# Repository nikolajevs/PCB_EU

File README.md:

# PCB_EU — контроллер гроубокса

Самостоятельный проект платы EU-0.1 и прошивки для ESP32-WROOM-32E-N4 (4 МБ flash, без PSRAM).

- [Аппаратная часть](hardware/PCB_EU/README.md): схема, плата, BOM, библиотеки, 3D-модели и результаты проверок.
- [Решения и ограничения](hardware/PCB_EU/DESIGN.md): питание, GPIO, механика и оставшиеся испытания.
- [Прошивка и инструкции сборки](softwareEU/README.md): климат, свет, вентиляторы, полив, RTC MCP7940N, INA226 и веб-интерфейс.
- [Трафареты для паяльной пасты](hardware/stencil/README.md): два печатных трафарета (верх и низ) под сопло 0,2 мм; не печатались.
- [Проект KiCad](hardware/PCB_EU/PCB_EU.kicad_pro): открывать в KiCad **10.0.7**.
- [EU-LITE](hardware/PCB_EU_LITE/README.md): удешёвленный аналог EU-0.1 из деталей со склада (один LED-канал, без тахометров), RGB-светодиод статуса, схема и BOM без PCB; закупка 34,68 € по каталогу от 23.10.2026 (RGB-светодиода в каталоге нет, оценка до 0,50 €).

## Состояние

Исходники перенесены 23.10.2026 из [nikolajevs/ai, коммит 390374e](https://github.com/nikolajevs/ai/tree/390374ec6d7405bd25f6ed4380bc14fe30cf3cde), включая исправления документации из [PR #93](https://github.com/nikolajevs/ai/pull/93). Затем 24.10.2026 перенесён [PR #94](https://github.com/nikolajevs/ai/pull/94) того же репозитория ([коммит 7fa9410](https://github.com/nikolajevs/ai/tree/7fa9410ddb7977c46e313506acb037693ad571e1)): D501/D601 — SS8PH10-M3/86A, J201 — ZL201-10G, клеммы DG306/DG301R без запаса; оценка закупки 84,67 € → 81,25 €. История предыдущей разработки остаётся в исходном репозитории; номера прежних PR в документации относятся к нему. PCB_V1, её прошивка и инфраструктура VPS в этот репозиторий не входят.

Сохранённые аппаратные отчёты относятся к полному прогону KiCad 10.0.7 от 23.10.2026, выполненному в исходном репозитории (PR #94): ERC и DRC без ошибок, плата полностью разведена. Повторный прогон в этом репозитории 24.10.2026 дал тот же результат, но не сохранялся. 24.10.2026 подготовлены Gerber и сверловка для платы из коммита `b3f286d`; Игорь подтвердил размещение заказа. [Заказанный архив и отчёт проверок](hardware/PCB_EU/README.md#заказ-платы-24102026) сохранены в репозитории. Испытания на реальной плате ещё предстоят.

**EU-LITE** (24.10.2026) — отдельный проект в `hardware/PCB_EU_LITE/`; EU-0.1 и заказанная плата не затронуты. Схема и BOM EU-LITE проверены только скриптами без KiCad; ERC, PCB и прошивка для неё ещё не выполнялись.

Радиатор Q501 крепится на двух запаянных ножках и винте М3 с изолирующей прокладкой и втулкой. Физическая примерка и проверка изоляции выполняются на прототипе.

## Проверки и сборка

Команды выполняются из корня репозитория. Для базовых проверок нужны Python 3 и Node.js:

```sh
python hardware/PCB_EU/tools/generate.py
python hardware/PCB_EU/tools/verify.py hardware/PCB_EU/review/netlist.xml
node --test tests/settings.test.cjs
```

Полная аппаратная проверка требует KiCad 10.0.7, Python с `pcbnew` той же версии и Shapely 2:

```sh
python hardware/PCB_EU/tools/run_checks.py --kicad-cli /path/to/kicad-cli --kicad-python /path/to/python-with-pcbnew
```

Общий скрипт `hardware/check_fab.py` включён в репозиторий: его вызывает `run_checks.py`. Исторические упоминания PCB_V1 в комментариях описывают происхождение кода, внешняя копия PCB_V1 для запуска не нужна. Все библиотеки и 3D-модели проекта находятся внутри `hardware/PCB_EU/libraries/`.

Сборка прошивки после установки зависимостей из [softwareEU/README.md](softwareEU/README.md#сборка-и-проверки):

```sh
arduino-cli compile --fqbn esp32:esp32:esp32 softwareEU
```

Файлы `softwareEU/data/` загружаются в SPIFFS отдельно. Список стендовых испытаний приведён в инструкции прошивки.

Проверки при переносе: 23.10.2026 — генерация без содержательных изменений, 56 проверок соединений и закупки, 10 тестов веб-интерфейса, проверка локальных ссылок и синтаксиса Python; полный аппаратный прогон тогда не повторялся. 24.10.2026 (PR #94) — то же и полный `run_checks.py` на KiCad 10.0.7; сохранённые отчёты `review/` отличаются от нового прогона только датами и путём в `netlist.xml`, поэтому не перезаписывались. На момент прогона контрольные суммы всех 123 исходников из `review/validation.json` совпадали с файлами. После уточнения BOM 24.10.2026 (домашние хидеры, поштучная продажа INA226, актуальные примечания) BOM и скрипты изменены; сохранённые контрольные суммы и сводка закупки относятся к предыдущему состоянию. Подробности — в README аппаратной части; схема и PCB не менялись. Сборка прошивки не выполнялась. Окончания строк текста закреплены в `.gitattributes`, исходные байты моделей STEP/STP сохраняются.

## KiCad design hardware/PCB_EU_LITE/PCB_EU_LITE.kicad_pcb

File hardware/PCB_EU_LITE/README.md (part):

# EU-LITE — дешёвый аналог EU-0.1 из деталей со склада

**Состояние на 26.10.2026: документация согласована с текущими исходниками; стендовые испытания не выполнены.** Плата 100×100 мм, четыре слоя, 163 посадки. Исправлены силовая медь входа и LED-каскада, переходные в пасте и локальная земля ESP32. Подключение Q102/Q701/Q702/Q703, ST1S14 и ST1S10 сохранено: замечание о перепутанных выводах снято.

**Выпуск изготовления пока не закрыт.** Последний полный прогон KiCad 10.0.7 сохранён в [review/power-copper-2026-10-26/](review/power-copper-2026-10-26/), но предшествует исправлению подписи F103. Сейчас схема содержит `6.3 A fast`, плата — старое поле `6.3 A slow`: электрические соединения совпадают, строгий паритет и `fabricate.py` не проходят из-за этого поля. Gerber r1/r2 устарели относительно текущей меди. Перед изготовлением нужно согласовать поле F103, повторить полный профиль и выпустить новый комплект Gerber/Excellon. Эта редакция документации схему, плату, BOM и отчёты проверок не изменяет.

Проект по образцу [cheap-version](https://github.com/nikolajevs/ai/tree/7fa9410ddb7977c46e313506acb037693ad571e1/hardware/cheap-version) (дешёвая PCB_V1 из того же склада): всё, что есть на складе владельца ([stock/sklad-2026-10-24.csv](stock/sklad-2026-10-24.csv)), берётся оттуда; недостающее — из [снимка каталога цен Salvats / Electrobase от 23.10.2026](procurement_lite.json). Отличия от EU-0.1, расчёты и открытые вопросы — в [DESIGN.md](DESIGN.md).

**F103:** `3413.0224.11` — SCHURTER **USI 1206, 6,3 А, Quick-Acting F (fast)** ([даташит](https://us.schurter.com/pdf/english/typ_usi_1206.pdf)). MPN и BOM сохранены; пуск LED и согласование I²t требуют измерения. F101 `3413.0330.11` и F102 `3413.0327.11` — UST 1206 time-lag; название карточки магазина не заменяет характеристику изготовителя.

## Что сохранено и что убрано

Сохранено: вход 24 В с защитой от переполюсовки и предохранителями, ESP32-WROOM-32E-N4 (те же GPIO), 12 В и 3,3 В, **один** LED-канал LM3429 (около 75 Вт / 1,55 А при 48 В суммарно на J501/J502/J503), **RGB-светодиод статуса** (GPIO4/16/17), PTC 100 Вт, помпа 24 В, два вентилятора 12 В с PWM, измерение мощности (INA238 вместо INA226), RTC MCP7940N с CR2032, microSD, SHT4x и поплавок.

Добавлено по просьбе владельца 24.10.2026: RGB-светодиод для индикации статуса и процессов (лист «Status»).

Убрано по решению владельца 24.10.2026: второй LED-канал (линейки) и тахометры вентиляторов. Дополнительно, для цены: аппаратная блокировка LED по UVLO/PGOOD (LM2903 + BAT54), USBLC6 на входе поплавка, ESD-диоды вентиляторов и радиатор с изоляцией. Последствия — в [DESIGN.md](DESIGN.md#отличия-от-eu-01) и [DESIGN.md, «Открытые вопросы»](DESIGN.md#открытые-вопросы).

## Файлы

| Файл | Назначение |
|---|---|
| [DESIGN.md](DESIGN.md) | Решения, отличия от EU-0.1, расчёты, склад без запаса, открытые вопросы |
| [PCB_EU_LITE.kicad_pro](PCB_EU_LITE.kicad_pro), [PCB_EU_LITE.kicad_sch](PCB_EU_LITE.kicad_sch) и 8 листов | Схема (KiCad 10, генерируется `tools/generate.py`) |
| [PCB_EU_LITE.kicad_pcb](PCB_EU_LITE.kicad_pcb), [placement.json](placement.json) | 163 посадки, четырёхслойная плата; статус паритета и изготовления — в разделе «Проверки» |
| [BOM_allocated.csv](BOM_allocated.csv), [BOM_allocated.json](BOM_allocated.json) | Склад (`stock`, с остатком после сборки) и докупка (`buy`, с URL и датой цены) |
| [procurement_lite.json](procurement_lite.json) | Снимок каталога с резисторами уставки LED 4,7 кОм/620 Ом и карточкой OSTAPA57E2A владельца |
| [stock/sklad-2026-10-24.csv](stock/sklad-2026-10-24.csv) | Склад владельца (копия присланной выгрузки) |
| [design.json](design.json) | Полная спецификация выводов, цепей и компонентов |
| [review/connectivity.txt](review/connectivity.txt) | Сохранённый предыдущий полный прогон; актуальные 58 проверок для 75 Вт описаны в разделе «Проверки» |
| [review/Bench_checklist.md](review/Bench_checklist.md) | Что измерить при первом включении |
| [review/silkscreen.json](review/silkscreen.json) | Аудит воспроизводимой сборочной шелкографии: размещённые, нативные и намеренно пропущенные метки |
| [libraries/](libraries) | Символы проекта; собственные посадки PowerDI5, DTMSS-27, VSSOP-10 и SOIC-8; локальная копия BC-2001 с узким коридором GND только для EU-LITE и локальные копии складских посадок; стандартные 3D-модели используют установленную библиотеку KiCad |
| [tools/route_power.py](tools/route_power.py), [tools/route_complete.py](tools/route_complete.py), [tools/route_progress.py](tools/route_progress.py), [tools/route_bt_ground.py](tools/route_bt_ground.py), [tools/route_rtc.py](tools/route_rtc.py), [tools/route_switch_stage.py](tools/route_switch_stage.py), [tools/route_ground_stitch.py](tools/route_ground_stitch.py), [tools/route_prune_stubs.py](tools/route_prune_stubs.py), [tools/route_led_source.py](tools/route_led_source.py), [tools/route_led_terminals.py](tools/route_led_terminals.py), [tools/silkscreen.py](tools/silkscreen.py) | Полигонная медь, воспроизводимые шаги частичной разводки и финальная сборочная шелкография |

`EU_Mechanical` и `EU_Parts` по-прежнему общие с EU-0.1 (`../PCB_EU/libraries`, см. `fp-lib-table`); исключение — `LITE_Mechanical:Battery_COMF_BC-2001`, локальная копия с коридором GND для батарейного контакта. Исходные библиотеки EU-0.1 не менялись.

## Закупка

**Electrobase** — 20,06 € с НДС (0,85 € — цена из карточки, присланной владельцем 25.10.2026)

| Деталь (артикул) | Шт. к покупке | Цена, € | Сумма, € | Позиции на плате |
|---|---:|---:|---:|---|
| [ABS07-32.768KHZ-7-T](https://electrobase.lv/katalogs/kvarca-generatori-tht/resonator-ceramic-32768khz-20ppm-7pf-smd-32x15x09mm) | 1 | 0.79 | 0.79 | Y301 |
| [AO3422](https://electrobase.lv/katalogs/tranzistori-ar-n-veida-kanalu-smd/transistor-n-mosfet-unipolar-55v-17a-800mw-sot23) | 5 (пачка по 5, нужно 3) | 0.26 | 1.30 | Q411 Q421 Q704 |
| [C1206C100J5GACTU](https://electrobase.lv/katalogs/kondensatori-mlcc-smd-0201/capacitor-ceramic-mlcc-10pf-50vdc-c0g-5-smd-1206) | 2 | 0.25 | 0.50 | C301 C302 |
| [ESP32-WROOM-32E-N4](https://electrobase.lv/katalogs/moduli-iot-wifi-bluetooth-lora/module-iot-bluetooth-low-energywifi-smd-0) | 1 | 7.48 | 7.48 | U202 |
| [JNRH1207-220M-A](https://electrobase.lv/katalogs/induktori-tht/inductor-wire-smd-22uh-ioper-54a-r-525o-30-isat-56a) | 1 | 0.54 | 0.54 | L101 |
| [OSTAPA57E2A](https://electrobase.lv/katalogs/diodes-led-tht-18mm/led-rgb-5mm-140deg-front-convex-231vdc-noof-term-4-round) | 1 | 0.85 | 0.85 | D901 |
| [LM3429MH/NOPB](https://electrobase.lv/katalogs/led-draiveri/ic-driver-boostbuck-boost-led-driver-htssop14-5a-372v-ch-1) | 1 | 4.86 | 4.86 | U501 |
| [MCP7940N-I/SN](https://electrobase.lv/katalogs/rtc-shemas/ic-rtc-circuit-i2c-sram-64bsram-1855vdc-so8-4085degc-tube-0) | 1 | 1.50 | 1.50 | U301 |
| [MEM2061-01-188-00-A](https://electrobase.lv/katalogs/savienojumi-kartem/connector-cards-microsd-push-push-smt-gold-flash-pin-8-0) | 1 | 1.74 | 1.74 | J301 |
| [SMBJ26A-E3/52](https://electrobase.lv/katalogs/diodes-transil-smd-vienvirziena/diode-tvs-600w-289319v-143a-unidirectional-5-smbj) | 1 | 0.50 | 0.50 | D101 |

**Salvats** — 12,56 € с НДС

| Деталь (артикул) | Шт. к покупке | Цена, € | Сумма, € | Позиции на плате |
|---|---:|---:|---:|---|
| [3403.0166.11](https://www.salvats.lv/lv/drosinataji-smd-10x3x3mm-umt-leni/1a-umt-drosinataji-leni-250vac125vdc-101x3x3mm-smd) | 1 | 0.75 | 0.75 | F105 |
| [3403.0169.11](https://www.salvats.lv/lv/drosinataji-smd-10x3x3mm-umt-leni/2a-umt-drosinataji-leni-250vac125vdc-101x3x3mm-smd) | 2 | 0.78 | 1.56 | F104 F401 |
| [3413.0224.11](https://www.salvats.lv/lv/drosinataji-smd-1206-32x16x06mm/drosinatajs-smd-1206-63a-63v-fast) | 1 | 0.86 | 0.86 | F103 |
| [3413.0327.11](https://www.salvats.lv/lv/drosinataji-smd-1206-32x16x06mm/drosinatajs-smd-1206-8a-63v-fast) | 1 | 0.80 | 0.80 | F102 |
| [3413.0330.11](https://www.salvats.lv/lv/drosinataji-smd-1206-32x16x06mm/drosinatajs-smd-1206-15a-63v-fast) | 1 | 0.75 | 0.75 | F101 |
| [BAT-CR2032/P](https://www.salvats.lv/lv/litija-baterijas/cr2032-litija-baterija-30v-o20x32mm-panasonic-442g) | 1 | 0.75 | 0.75 | комплектующее (CR2032 для BT301) |
| [BC-2001](https://www.salvats.lv/lv/baterijas-turetaji-1/bateriju-turetajs-metaliska-cemme-cr2032-1-baterija) | 1 | 0.33 | 0.33 | BT301 |
| [BC847B-DIO](https://www.salvats.lv/lv/npn-tranzistori-smd/bc847b1f-smd-tranzistors-npn-50v-01a-300mhz-sot23) | 4 | 0.06 | 0.24 | Q701 Q901 Q902 Q903 |
| [BC857B](https://www.salvats.lv/lv/pnp-tranzistori-smd/bc857b3f-smd-tranzistors-pnp-50v-01a-hfe220475-035w-200mhz-sot23) | 1 | 0.08 | 0.08 | Q702 |
| [BZV55C12](https://www.salvats.lv/lv/stabilitroni-smd-bzv55/12v-stabilitrons-smd-bzv55-5-05w-minimelf) | 1 | 0.13 | 0.13 | D103 |
| [C1206C102JCGACTU](https://www.salvats.lv/lv/kondensatori-keramiskie-smd-1206-1/1nf-1206-c0g-500v-5-smd-kondensators-1206) | 1 | 0.25 | 0.25 | C506 |
| [CL31C101JBCNNNC](https://www.salvats.lv/lv/kondensatori-keramiskie-smd-1206-1/100pf-1206-npo-50j-smd-kondensators-1206) | 1 | 0.07 | 0.07 | C507 |
| [CRCW1206620RFKTABC](https://www.salvats.lv/lv/rezistori-smd-1206-025w/620r-1206-1-smd-rezistors-1206) | 1 | 0.03 | 0.03 | R506 |
| [CRCW120682K0FKTABC](https://www.salvats.lv/lv/rezistori-smd-1206-025w/82k-1206-1-smd-rezistors-1206) | 1 | 0.03 | 0.03 | R101 |
| [CS2512-0R15-1%-HP](https://www.salvats.lv/lv/rezistori-smd-2512-1w3w/0r15-2512635x32mm-2w-1-smd-55125c-rezistors-thick-film-2512) | 1 | 0.32 | 0.32 | R502 |
| [CSD19531KCS](https://www.salvats.lv/lv/100v-n-fet-tht/csd19531kcs-tranzistors-n-fet-100v-vgs2233v-20v-100a-214w-0r0073-to-220) | 1 | 2.95 | 2.95 | Q703 |
| [LRP2512-R040-1%](https://www.salvats.lv/lv/rezistori-smd-2512-1w3w/0r04-2512635x32mm-3w-1-smd-55170c-rezistors-thick-film-2512) | 1 | 0.38 | 0.38 | R501 |
| [SMD1206 4K7 1%](https://www.salvats.lv/lv/rezistori-smd-1206-025w/4k7-1206-1-smd-rezistors-1206) | 1 | 0.04 | 0.04 | R505 |
| [SMD1206 56K 1%](https://www.salvats.lv/lv/rezistori-smd-1206-025w/56k-1206-1-smd-rezistors-1206) | 1 | 0.03 | 0.03 | R507 |
| [SMD1206-10K-1%](https://www.salvats.lv/lv/rezistori-smd-1206-025w/10k-1206-1-smd-rezistors-1206) | 1 | 0.03 | 0.03 | R108 |
| [SMD1206-33K-1%](https://www.salvats.lv/lv/rezistori-smd-1206-025w/33k-1206-1-smd-rezistors-1206) | 1 | 0.03 | 0.03 | R509 |
| [SMD1206-6K2-1%](https://www.salvats.lv/lv/rezistori-smd-1206-025w/6k2-1206-1-smd-rezistors-1206) | 2 | 0.03 | 0.06 | R102 R508 |
| [UPW1H221MPD](https://www.salvats.lv/lv/kondensatori-elektrolitiskie-zemas-induktivitates-low-esr/22050v-105c-o10x16mm-20-kondensatori-zemas-induktivitates-011r-5000h-nichicon-ar-lokaniem-izvadiem) | 2 | 0.63 | 1.26 | C101 C102 |
| [USBLC6-2SC6](https://www.salvats.lv/lv/u/usblc6-2sc6-smd-mikroshema-esd-protection-sot23-6) | 1 | 0.67 | 0.67 | U401 |
| [ZL201-10G](https://www.salvats.lv/lv/listes-un-nuju-ligzdas/254mm-uz-pcb-10pin-stekers-1) | 1 | 0.16 | 0.16 | J201 |

Со склада идёт 115 шт. в 38 позициях. KF301 используются 7 из 31 шт., остаётся 24; два новых клеммника не требуют закупки. Новые резисторы уставки LED добавляют 0,01 € к прежней сумме. Для Q703 выбран каталожный CSD19531KCS в TO-220; один BSC146N10LS5 остаётся в запасе для Q501. Без запаса остаются INA238, IRL2505, дроссель DTMSS-27 и два электролита EEVFK1J471M/EEEFT1E821AP. Полный список с остатками — [BOM_allocated.csv](BOM_allocated.csv).

Для D901 выбран OPTOSUPPLY OSTAPA57E2A. Цена 0,85 € с НДС и остаток 99 шт. взяты из карточки Electrobase, присланной владельцем 25.10.2026; наличие через корзину отдельно не проверялось. CSD19531KCS для Q703 добавлен из `catalog.db`: Salvats, 2,95 € с НДС, остаток 7 шт. в снимке от 23.10.2026; корзина не проверялась. Остальные цены и остатки — снимок каталога от 23.10.2026; C1206C100J5GACTU — из BOM EU-0.1 от 23.10.2026. Доставка 2,99 € (Electrobase) + 2,88 € (Salvats) взята из README EU-0.1 и не перепроверялась. Это не оферта и не заказ. AO3422 продаётся пачками по 5: два лишних.

## Проверки

Результаты относятся к указанным состояниям проекта, а не к новому запуску при редактировании документации.

| Состояние | Результат и ограничение |
|---|---|
| Последний полный прогон меди, KiCad 10.0.7, 26.10.2026 | [Сводка](review/power-copper-2026-10-26/summary.json): ERC пройден; 0 электрических/геометрических ошибок DRC, 0 неподключённых цепей и 0 расхождений на момент прогона; 35 библиотечных предупреждений проверены как отличия только шелкографии; экспорт и независимый CAM-импорт пройдены |
| Размещение в том же прогоне | [18 791 проверка](review/power-copper-2026-10-26/placement.json), 163 посадки, 437 подключённых выводов; стороны: 125 сверху и 38 снизу |
| Силовые пути в том же прогоне | [Проверка геометрии](review/power-copper-2026-10-26/power_paths.json): 10 входных переходных связаны с J101/F101 на обеих сторонах, 0 пересечений пасты, 7 GND-переходных у ESP32, силовые LED_SW/LED_OUT/LED_POS отсутствуют на внутренних слоях |
| После исправления подписи F103 | Свежий экспорт подтвердил неизменность всех 437 подключённых узлов; ERC, 58 проверок `verify.py`, проверка схем и мутационные тесты пройдены. DRC: 0 электрических/геометрических ошибок, 0 неподключённых цепей, 35 прежних предупреждений и 1 текстовое расхождение Value F103 |
| Полный профиль после исправления F103 | **Не пройден:** `check_placement.py` останавливается на `F103: value differs`; новый производственный комплект не выпущен. Правила не ослаблялись |
| Архивы изготовления r1/r2 | Исторические комплекты для прежней меди; **не использовать для текущей платы** |
| Физические испытания | Не выполнены: сборка, корпус, пуск, динамика шин, нагрев и прошивка требуют [стендовой проверки](review/Bench_checklist.md) |

Сохранённые отчёты не перезаписываются частичной проверкой. Для нового выпуска нужен полный `tools/fabricate.py` на KiCad 10.0.7 с Python `pcbnew` той же версии, Shapely 2 и gerbonara; каталог результата должен быть новым:

```sh
python hardware/PCB_EU_LITE/tools/fabricate.py --kicad-cli /path/to/kicad-cli --output /path/to/new-release
```

Это проверка и экспорт существующих исходников; до согласования Value F103 ожидается остановка на проверке размещения.

**Размещение.** Все 163 посадочных места схемы находятся внутри платы 100×100 мм: 125 сверху, 37 SMD и BT301 с CR2032 снизу. Сохранены 4 отверстия и четырёхслойный стек. Сверху оставлены высокие и силовые компоненты; снизу размещены RGB, подтяжки microSD, RTC у батарейки, делитель вспомогательного БП и маломощное управление нагрузками. KiCad DRC и нативные проверки куртяр/коридоров прошли; физический корпус, высота деталей и ручная сборка не проверены.

**LED-выходы и мощность (25.10.2026).** Справа теперь три одинаковых KF301-2P: J501 (94;61), J502 (94;74), J503 (94;87) мм, все сверху под 90°. Вывод 1 — LED_POS после шунта R502, вывод 2 — GND; общий плюс соединён дорожкой 1 мм и локальной заливкой по F.Cu. Все три разъёма делят **один** токовый канал. R505/R506 = **4,7 кОм + 620 Ом, 1%, 1206**: примерно 1,55 А и 75 Вт суммарно при 48 В. Номинальная модель по таблице TI даёт 1,548 А / 74,3 Вт. Путь истоков Q501 к R501 теперь 0,8 мм по F.Cu с отдельной ветвью от каждого вывода; съём U501.12/TP04 сохранён у шунта.

Расчёт при 21,6 В, КПД 90%, L=43,5 мкГн, 400 кГц и допусках уставки: пик до **4,36 А**, минимальный IS-порог **5,32 А**, запас около **22%**. Нагрев не подтверждён. Общий бюджет с PTC/помпой/вентиляторами — до 8,7 А в модели, проектный предел 9 А; БП требуется 24 В / 10 А. Для 75 Вт в прошивке нужно поднять минимум nDIM до **5 отсчётов при 1 кГц/8 бит = 19,53 мкс**; сейчас `softwareEU/Board.h` даёт 3 отсчёта, эта правка и адаптация INA238 остаются открытыми. Подключаемые параллельно LED-ветви должны иметь согласованные Vf; деление тока между ними подтверждается измерением. [Расчёты и источники](DESIGN.md#led-канал).

**Симуляция LED-каскада (25.10.2026).** `tools/led_boost_simulation.py` рассчитывает установившийся режим при Vin 21,6/24/25 В и отдельно угол верхнего тока 1,627 А при 21,6 В. Для номинальной суммарной нагрузки 48 В / 1,548 А пики L501 — 3,895/3,536/3,405 А; в углу — 4,081 А. Duty подбирается к заданной рабочей точке: это условие расчёта, а не подтверждение регулирования реального LM3429. Сходимость проверена уменьшением шага примерно с 25 до 12,5 нс, балансом энергии и независимым тестом идеального boost. [Отчёт и график](review/LED_boost_simulation.md). Прежний расчёт с КПД 90% (пик 4,36 А) сохраняется как более консервативный; пуск, COMP, nDIM, OVP/КЗ, нагрев и деление тока между LED-ветвями требуют отдельной проверки.

**Разводка (26.10.2026).** После штатного `finalize_board.py` применяется `tools/repair_power.py`. Скрипт освобождает верхний путь F103–L501 от трёх малоточных пересечений, проводит питание дросселя и C501 дорожками 2 мм F.Cu, L501–Q501 — 2 мм F.Cu, L501–D501 и перемычку двух анодных площадок D501 — 1,2 мм F.Cu. Внутренний крючок LED_SW удалён. LED_OUT и LED_POS больше не используют In2.Cu: основная подача к J501 — 1,2 мм, остальные силовые ответвления — 0,8 мм по внешней меди; измерительные ответвления и развязка — 0,25 мм. Внутренний слой может использоваться только для малоточных ветвей питания контроллера, а не для подачи к дросселю. Массив у F101 содержит 10 переходных 0,8/0,4 мм; для него локально переложены соседние GPIO и ветвь +24V_FUSED. Проверка `check_power_paths.py` требует, чтобы каждое отверстие массива попадало в непрерывную F.Cu-медь до F101.1 и B.Cu-медь до J101.1, а не просто имело правильное имя цепи. Обратка PSU_RTN усилена внешним коридором шириной 5 мм на свободном участке; внутренняя полоса остаётся параллельной. Kelvin-keepout INA238 сохраняется.

RTC U301, Y301, C301/C302/C303 остаются на B.Cu у батарейки; кварцевые цепи без vias, VBAT/I²C/+3V3 подключены. Общие подтяжки R308/R309 остались у ответвления I²C. Держатель BT301 подключён к GND через коридор нижней стороны и via вне держателя.

**Разъёмы и слот (25.10.2026).** Справа сверху вниз: SHT4x J401, FAN1 J411, FAN2 J421 и три параллельных LED-клеммника J501/J502/J503. Снизу: FLOAT J403, PTC J701 и PUMP J702. Вход 24 В J101 перенесён налево. UART J201 оставлен на координатах (4; 9,75) мм с прежней ориентацией, microSD J301 — у левого края под UART, карта выходит влево. Между их куртярами около 3 мм. В `placement.json` записаны направления подключения и коридоры доступа длиной 20 мм, шириной по корпусу +0,5 мм с каждого края; они проверяются против компонентов и крепежа. Это проектный резерв, не проверка конкретного штекера, радиуса изгиба кабеля или стенки корпуса.

**J411/J421 — угловые 90°, шаг 2,54 мм.** Новая локальная посадка `LITE_Parts:KF2510_1x04_P2.54mm_RightAngle` воспроизводится `tools/generate_connectors.py`. Геометрический ориентир — [чертёж производителя LHE, A2543-WR04 / 2510-4AW, стр. 14](https://www.lhecn.com/wp-content/uploads/2019/01/a25432510.pdf): шаг 2,54 мм, ширина 10,16 мм, габариты 11,5×5,7 мм. Отверстия 1,0 мм вместо указанных в чертеже 0,9 мм, площадки 1,8 мм и запас куртяра 0,5 мм — проектные решения. 3D — условная габаритная модель. Распиновка не менялась: 1 GND, 2 +12V, 3 NC, 4 PWM. Производитель, угловое исполнение и ключ складского «KF2510 / KF2540 4P» не подтверждены физически: перед монтажом сверить с фактической деталью. Учёт склада и сумма BOM не изменены.

**D901.** Для OSTAPA57E2A сделана отдельная THT-посадка с отверстием 1,0 мм и площадкой 1,8 мм; по даташиту выводы имеют ширину 0,5 ±0,1 мм и шаг 1,25 мм. Перед установкой выводы нужно развести до шага 2,54 мм. Это проектная формовка, её нужно примерить на фактическом светодиоде до пайки. Даташит изготовителя указывает плоский торец, карточка Electrobase называет корпус выпуклым. KiCad DRC больше не находит ошибок кольца.

**Воспроизводимость.** `build_board.py` берёт из EU-0.1 только контур и монтажные отверстия; электрические посадки читает из локальных библиотек, все поля и цепи — из свежего netlist, координаты — из `placement.json`. Медь и старые подписи EU-0.1 не переносятся. Сохранение платы изолировано от настоящего `.kicad_pro`: KiCad 10.0.5 больше не затирает его чужими/пустыми настройками. Генератор схем сохраняет регистрацию всех локальных библиотек. Исправлены пути общих 3D-моделей; для U101/U201 стандартная STEP-модель с точным именем отсутствует в установленной KiCad 10.0.5, её визуализация ещё не закрыта.

`tools/silkscreen.py` выполняется после всех шагов разводки. Он управляет отдельной группой сборочной шелкографии, сначала размещает позиции обычных компонентов, затем полезные обозначения контактов разъёмов; крупные подписи разъёмов не занимают место. Размер позиций — 1,0 мм, в плотных местах — не менее 0,8 мм согласно правилу платы; штрих у всех добавленных надписей — 0,15 мм. 125 из 163 позиций разместились без наложения на площадки, переходы, корпуса и штатную шелкографию; не поместившиеся на стороне своей детали перечислены в `review/power-copper-2026-10-26/silkscreen.json`. Метки F-деталей на B.Silk не переносятся: на боте остаются только позиции реально нижних деталей. Генератор предпочитает вертикальную позицию на стороне компонента; получились 29 вертикальных ссылок, включая разъёмы, где это возможно вне их контура. По решению владельца удалены все новые `K` и восемь нативных штрихов `+` у C101/C102/C110/C508; оставлены только нужные `+` BT301 и D901. У 17 деталей с нечётным числом реальных выводов генератор не добавляет полярность/pin-1; прочие нативные метки посадок не удаляются. Дополнительный проход подбирает положения по границам соседних препятствий и надписей: восстановлены 11 позиций сверху без перемещения прежних меток; на нижней стороне по-прежнему 36 позиций своих деталей. Для однозначности подпись не должна быть ближе к чужой детали, чем к своей.

Следующие команды — пересборка исходников и платы, а не проверка сохранённого файла. Выполнять только в отдельной рабочей копии: генераторы перезаписывают результаты. Для обычного выпуска использовать `fabricate.py` выше. Для Python требуется интерпретатор KiCad с Shapely 2:

```text
python hardware/PCB_EU_LITE/tools/generate_connectors.py
python hardware/PCB_EU_LITE/tools/generate.py
python hardware/PCB_EU_LITE/tools/generate_led.py
kicad-cli sch export netlist --format kicadxml -o NETLIST.xml hardware/PCB_EU_LITE/PCB_EU_LITE.kicad_sch
python hardware/PCB_EU_LITE/tools/build_board.py NETLIST.xml
python hardware/PCB_EU_LITE/tools/check_placement.py NETLIST.xml
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
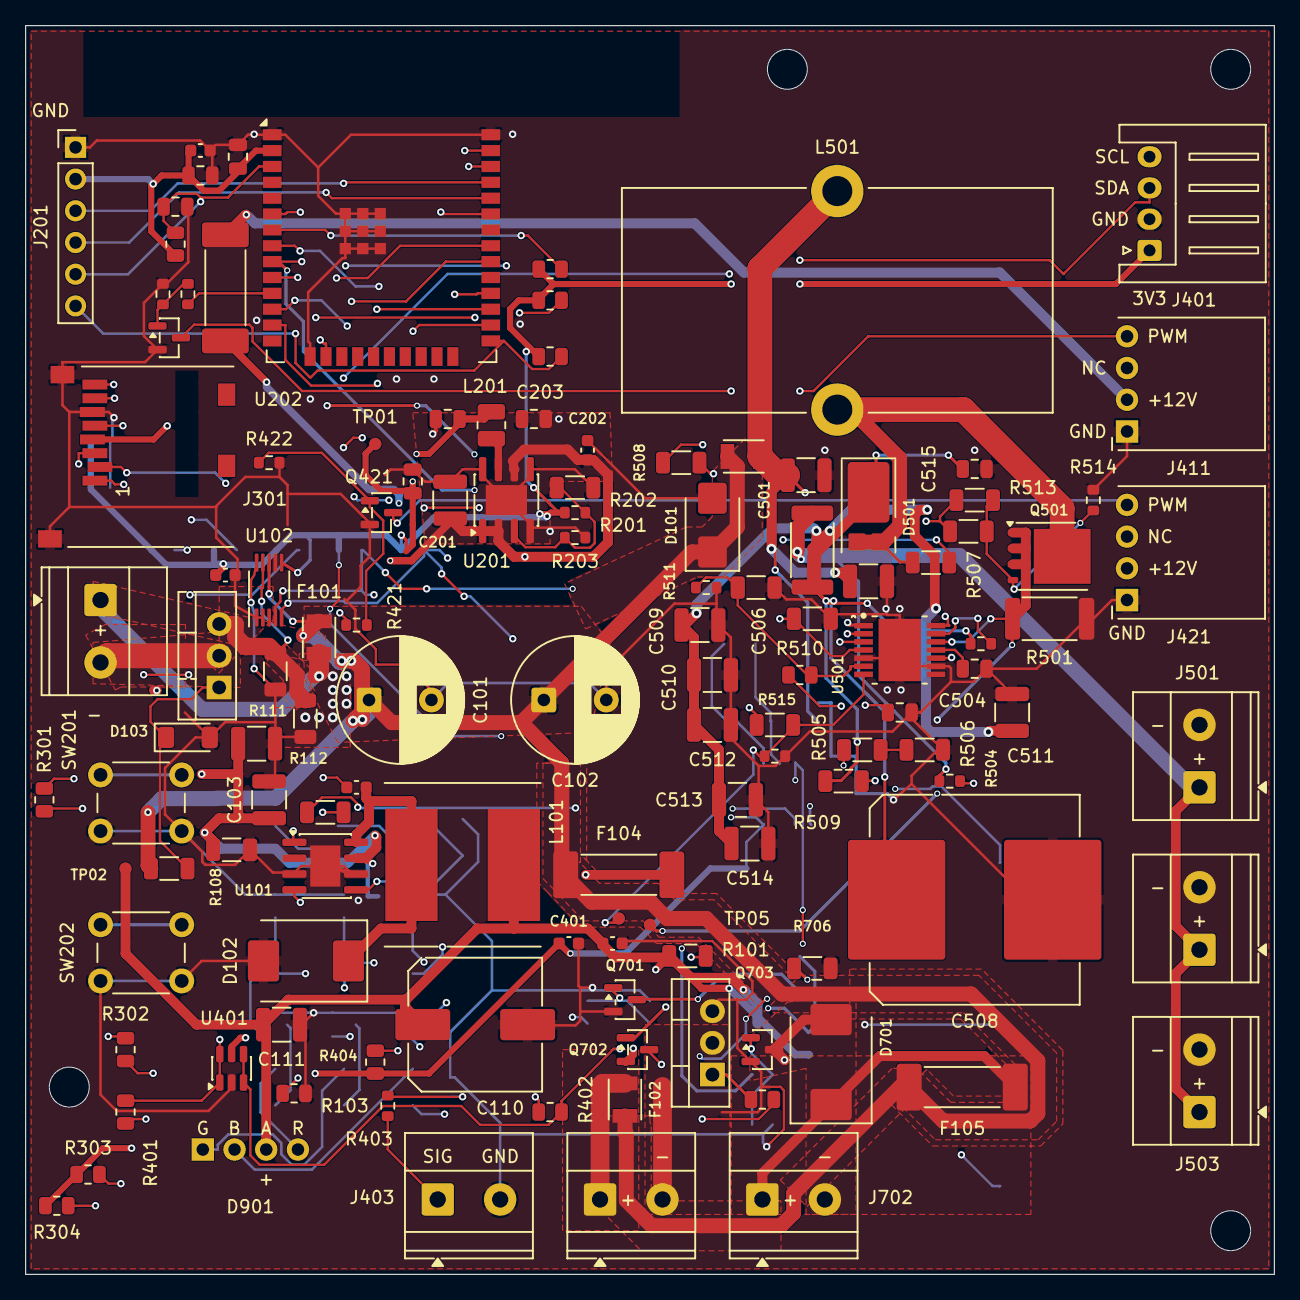
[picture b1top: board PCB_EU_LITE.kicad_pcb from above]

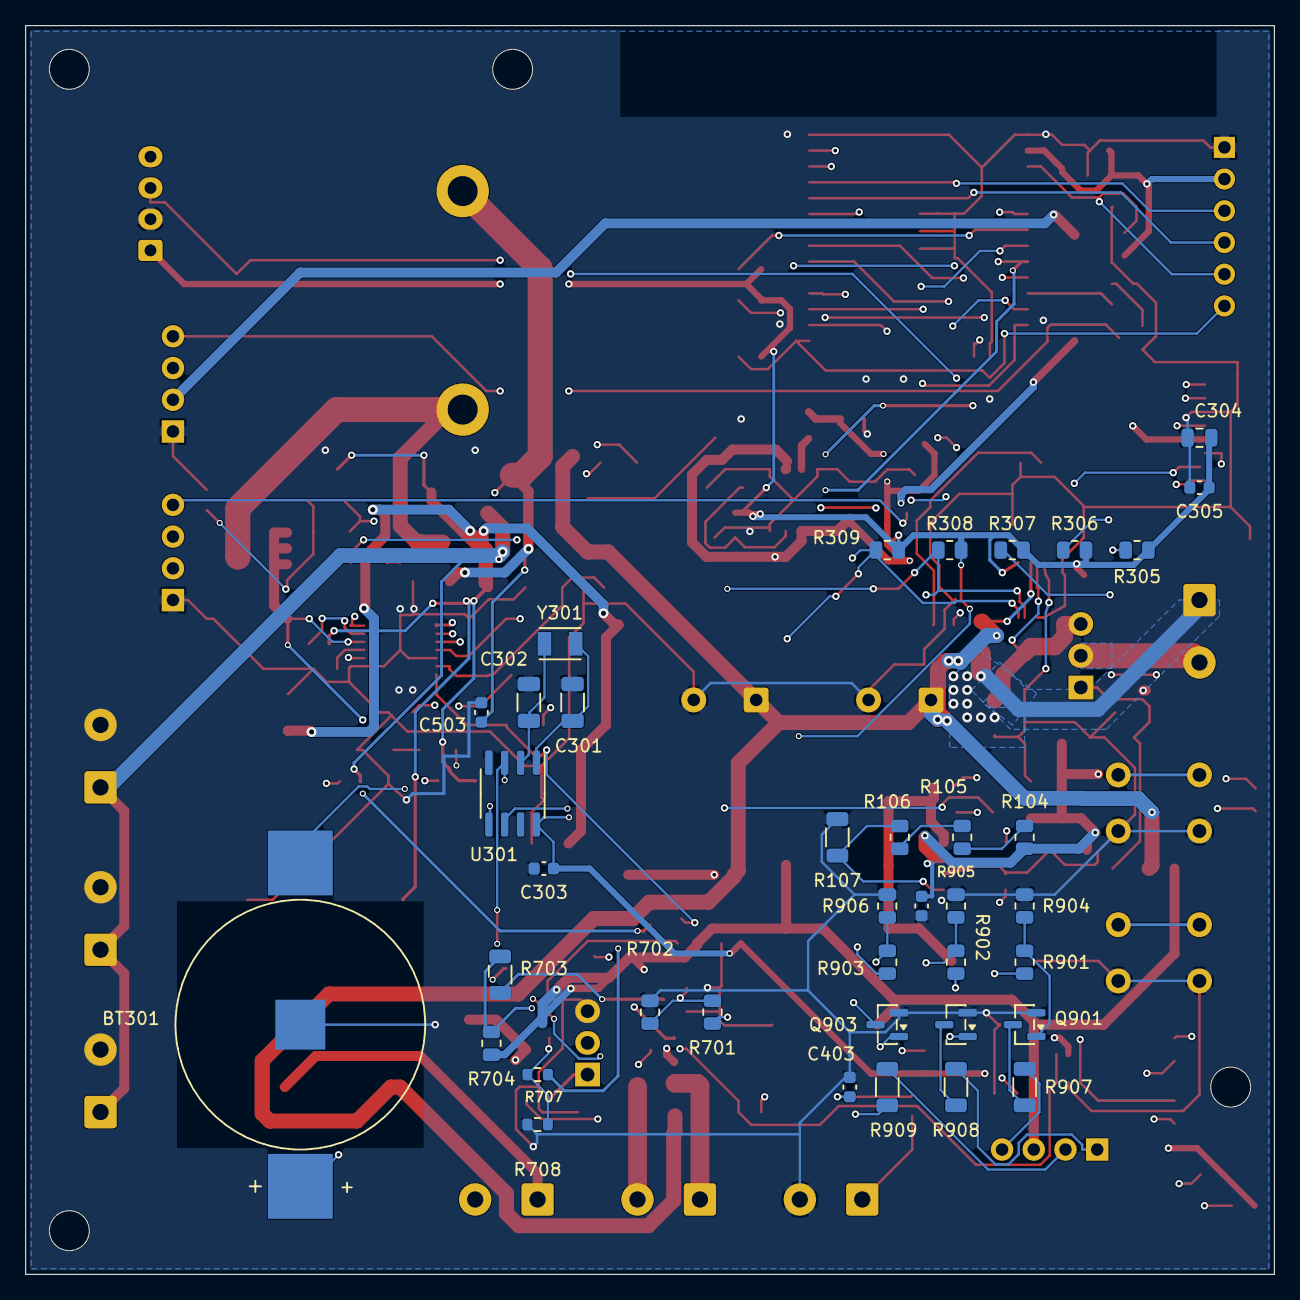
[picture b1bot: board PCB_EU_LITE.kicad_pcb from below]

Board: 4 copper layers, 100.0 x 100.0 mm, 167 parts (38 on the bottom side), 91 nets.

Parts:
BT301: CR2032 + BC-2001; Battery_COMF_BC-2001
C101, C102: 220u 50V; CP_Radial_D10.0mm_P5.00mm
C103, C104, C501, C502: 10u 50V; C_1210_3225Metric
C105: 2u2 50V; C_1206_3216Metric
C106: 100n BOOT; C_0603_1608Metric
C107: 100n HF; C_0603_1608Metric
C110: 820u 25V; CP_Elec_10x10.5
C111, C201: 10u 35V; C_1210_3225Metric
C112, C202, C208, C303, C305, C401: 100n; C_0603_1608Metric
C115: 100n VS; C_0603_1608Metric
C203: 2u2 VIN_A; C_0805_2012Metric
C204, C205, C206, C207, C304: 22u 10V; C_0805_2012Metric
C209: 2u2 RESET; C_0805_2012Metric
C301, C302: 10p C0G; C_1206_3216Metric
C403: 100n FILTER; C_0603_1608Metric
C503: 100n VIN; C_0603_1608Metric
C504: 4u7 25V; C_0805_2012Metric
C505: 22u COMP; C_0805_2012Metric
C506: 1n C0G; C_1206_3216Metric
C507: 100p C0G; C_1206_3216Metric
C508: 470u 63V; CP_Elec_16x17.5
C509, C510, C511, C512, C513, C514: 4u7 100V; C_1210_3225Metric
C515: 100n 100V; C_0805_2012Metric
D101: SMBJ26A; D_SMB
D102, D701: SS56 60V 5A; D_SMC
D103: BZV55C12 12 V; D_MiniMELF
D501: SBRT15U100SP5; Diodes_PowerDI5
D901: OSTAPA57E2A; LED_OSTAPA57E2A_Formed_P2.54mm
F101: 15 A slow; Fuse_Schurter_UST_USI1206_Reflow
F102: 8 A slow; Fuse_Schurter_UST_USI1206_Reflow
F103: 6.3 A slow; Fuse_Schurter_UST_USI1206_Reflow
F104, F401: 2 A slow; Fuse_Schurter_UMT250
F105: 1 A slow; Fuse_Schurter_UMT250
H1, H2, H3, H4: M3 NPTH 3.2 / proposed
J101: 24 V IN; TerminalBlock_Phoenix_MKDS-1,5-2_1x02_P5.00mm_Horizontal
J201: UART 3V3; PinHeader_1x06_P2.54mm_Vertical
J301: MEM2061 SPI; microSD_GCT_MEM2061-01-188-00-A
J401: SHT4x XH2.54-4P-90; JST_XH_S4B-XH-A_1x04_P2.50mm_Horizontal
J403: FLOAT / GND; TerminalBlock_Phoenix_MKDS-1,5-2_1x02_P5.00mm_Horizontal
J411: FAN1 2510-4P 90deg; KF2510_1x04_P2.54mm_RightAngle
J421: FAN2 2510-4P 90deg; KF2510_1x04_P2.54mm_RightAngle
J501: LED + / GND; TerminalBlock_Phoenix_MKDS-1,5-2_1x02_P5.00mm_Horizontal
J502: LED 2 + / GND; TerminalBlock_Phoenix_MKDS-1,5-2_1x02_P5.00mm_Horizontal
J503: LED 3 + / GND; TerminalBlock_Phoenix_MKDS-1,5-2_1x02_P5.00mm_Horizontal
J701: PTC + / RETURN; TerminalBlock_Phoenix_MKDS-1,5-2_1x02_P5.00mm_Horizontal
J702: PUMP + / RETURN; TerminalBlock_Phoenix_MKDS-1,5-2_1x02_P5.00mm_Horizontal
L101: 22u; L_Jantek_JNRH1207
L201: 2u2; L_1008_2520Metric
L501: 47u 15A; L_Feryster_DTMSS-27_V
Q102: IRL2505; TO-220-3_Vertical
Q411: FAN1 AO3422; SOT-23
Q421: FAN2 AO3422; SOT-23
Q501: BSC146N10LS5; TDSON-8-1
Q701: BC847B-DIO; SOT-23
Q702: BC857B; SOT-23
Q703: CSD19531KCS; TO-220-3_Vertical
Q704: AO3422; SOT-23
Q901: BC847B (R); SOT-23
Q902: BC847B (G); SOT-23
Q903: BC847B (B); SOT-23
R101: 82k 1%; R_1206_3216Metric
R102, R508: 6k2 1%; R_1206_3216Metric
R103, R510: 10k 1%; R_0805_2012Metric
R104, R105, R106: 150k; R_0805_2012Metric
R107, R202: 47k 1%; R_1206_3216Metric
R108: 10k 1206; R_1206_3216Metric
R111, R112: 7m 1% 1W; R_1206_3216Metric
R201, R203: 100k 1%; R_0603_1608Metric
R204, R205, R206, R207, R303, R304, R305, R306, R307, R404, R701, R704: 10k; R_0805_2012Metric
R301, R302, R401, R402, R705: 100R; R_0805_2012Metric
R308, R309, R702, R901, R902, R903: 4k7; R_0805_2012Metric
R403: 1k; R_0603_1608Metric
R411, R421, R707: 1k GATE; R_0603_1608Metric
R412, R422, R514, R708: 100k; R_0603_1608Metric
R501: 0R040 3W; R_2512_6332Metric
R502: 0R15 2W; R_2512_6332Metric
R503, R504, R511: 1k 1%; R_0603_1608Metric
R505: 4k7 1%; R_1206_3216Metric
R506: 620R 1%; R_1206_3216Metric
R507: 56k 1%; R_1206_3216Metric
R509: 33k 1%; R_1206_3216Metric
R512, R513: 10R; R_1206_3216Metric
R515: 5k1; R_1206_3216Metric
R516: 10k SHARED; R_0603_1608Metric
R703, R706, R907, R908, R909: 2k; R_1206_3216Metric
R904, R905, R906: 100k; R_0805_2012Metric
SW201: RESET; SW_PUSH_6mm_H9.5mm
SW202: BOOT; SW_PUSH_6mm_H9.5mm
TP01: +3V3; TestPoint_Pad_D1.0mm
TP02: +12V; TestPoint_Pad_D1.0mm
TP03: LED_NDIM; TestPoint_Pad_D1.0mm
TP04: LED_IS; TestPoint_Pad_D1.0mm
TP05: +24V_FUSED; TestPoint_Pad_D1.0mm
U101: ST1S14PHR; SOIC-8-1EP_3.9x4.9mm_P1.27mm_EP2.41x3.3mm
U102: INA238; VSSOP-10_3x3mm_P0.5mm
U201: ST1S10PHR; SOIC-8-1EP_3.9x4.9mm_P1.27mm_EP2.41x3.3mm
U202: ESP32-WROOM-32E-N4; ESP32-WROOM-32E_NoVias
U301: MCP7940N; SOIC-8_3.9x4.9mm_P1.27mm
U401: USBLC6-2SC6; SOT-23-6
U501: LM3429MH/NOPB; TI_PWP0014A_LM3429
Y301: 32.768k CL7p; Crystal_Abracon_ABS07

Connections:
+3V3: C115.1, C204.1, C205.1, C206.1, C207.1, C208.1, C303.1, C304.1, C305.1, C401.1, J201.2, J301.4, J401.1, L201.2, R201.1, R204.1, R205.1, R206.1, R207.1, R303.1, R304.1, R305.1, R306.1, R307.1, R308.1, R309.1, R404.1, TP01.1, U102.6, U202.2, U301.8, U401.5
+12V: C110.1, C111.1, C112.1, C201.1, C202.1, C203.1, D901.3, F401.1, L101.2, Q702.2, R101.1, R704.1, TP02.1, U201.1, U201.2, U201.6
+12V_FANS: F401.2, J411.2, J421.2
+24V_AUX: C103.1, C104.1, C105.1, C107.1, F104.2, R104.1, U101.7
+24V_FUSED: C101.1, C102.1, D101.1, F101.2, F102.1, F103.1, F104.1, F105.1, R108.1, TP05.1, U102.8
+24V_LED: C501.1, C502.1, C503.1, F103.2, L501.1, U501.1
+24V_PTC: F102.2, J701.1
+24V_PUMP: D701.1, F105.2, J702.1
+24V_RAW: F101.1, J101.1
AUX_BOOT: C106.1, U101.1
AUX_EN2: R106.2, R107.1, U101.5
AUX_EN2_A: R104.2, R105.1
AUX_EN2_B: R105.2, R106.1
AUX_FB: R102.2, R103.1, U101.4
AUX_FB_MID: R101.2, R102.1
AUX_SW: C106.2, D102.1, L101.1, U101.8
ESP_BOOT: J201.6, R205.2, SW202.1, U202.25
ESP_EN: C209.1, J201.5, R204.2, SW201.1, U202.3
FAN1_GATE: Q411.1, R411.2, R412.1
FAN1_GPIO: R411.1, U202.11
FAN1_PWM: J411.4, Q411.3
FAN1_TACH: R206.2, U202.6
FAN2_GATE: Q421.1, R421.2, R422.1
FAN2_GPIO: R421.1, U202.12
FAN2_PWM: J421.4, Q421.3
FAN2_TACH: R207.2, U202.7
FLOAT_EXT: J403.1, R403.1
FLOAT_GPIO: C403.1, R403.2, R404.2, U202.13
GND: BT301.2, C101.2, C102.2, C103.2, C104.2, C105.2, C107.2, C110.2, C111.2, C112.2, C115.2, C201.2, C202.2, C203.2, C204.2, C205.2, C206.2, C207.2, C208.2, C209.2, C301.2, C302.2, C303.2, C304.2, C305.2, C401.2, C403.2, C501.2, C502.2, C503.2, C504.2, C505.2, C506.2, C507.2, C508.2, C509.2, C510.2, C511.2, C512.2, C513.2, C514.2, C515.2, D101.2, D102.2, D103.2, J201.1, J301.6, J301.SH, J401.2, J403.2, J411.1, J421.1, J501.2, J502.2, J503.2, Q411.2, Q421.2, Q701.2, Q703.3, Q704.2, Q901.2, Q902.2, Q903.2, R103.2, R107.2, R111.1, R112.1, R202.2, R203.2, R412.2, R422.2, R501.2, R506.2, R511.2, R514.2, R516.2, R702.2, R706.2, R708.2, R904.2, R905.2, R906.2, SW201.2, SW202.2, U101.3, U101.6, U101.9, U102.1, U102.2, U102.7, U102.10, U201.4, U201.5, U201.8, U201.9, U202.1, U202.15, U202.38, U202.39, U301.4, U401.2, U501.5, U501.9, U501.15
I2C_SCL: R309.2, R402.1, U102.5, U202.36, U301.6
I2C_SDA: R308.2, R401.1, U102.4, U202.33, U301.5
LED_B_BASE: Q903.1, R903.2, R906.1
LED_B_C: Q903.3, R909.1
LED_B_GPIO: R903.1, U202.28
LED_B_K: D901.2, R909.2
LED_COMP: C505.1, U501.2
LED_CSH: R505.1, U501.3
LED_CSH_MID: R505.2, R506.1
LED_GATE: Q501.4, R512.2, R513.2, R514.1
LED_GATE_RAW: R512.1, R513.1, U501.10
LED_G_BASE: Q902.1, R902.2, R905.1
LED_G_C: Q902.3, R908.1
LED_G_GPIO: R902.1, U202.27
LED_G_K: D901.1, R908.2
LED_HSN: R504.2, U501.14
LED_HSP: R503.2, U501.13
LED_IS: Q501.1, Q501.2, Q501.3, R501.1, TP04.1, U501.12
LED_NDIM: R515.2, R516.1, TP03.1, U501.7
LED_OUT: C508.1, C509.1, C510.1, C511.1, C512.1, C513.1, C514.1, C515.1, D501.1, R502.1, R503.1, R509.1
LED_OVP: C507.1, R510.2, R511.1, U501.6
LED_OVP_MID: R509.2, R510.1
LED_POS: J501.1, J502.1, J503.1, R502.2, R504.1
LED_PWM_GPIO: R515.1, U202.10
LED_RCT: C506.1, R508.2, U501.4
LED_RT_MID: R507.2, R508.1
LED_R_BASE: Q901.1, R901.2, R904.1
LED_R_C: Q901.3, R907.1
LED_R_GPIO: R901.1, U202.26
LED_R_K: D901.4, R907.2
LED_SW: D501.2, L501.2, Q501.5, R507.1
LED_VCC: C504.1, U501.11
LOGIC_FB: R201.2, R202.1, R203.1, U201.3
LOGIC_SW: L201.1, U201.7
PSU_RTN: J101.2, Q102.2
PTC_DRAIN: J701.2, Q703.2
PTC_DRV: Q702.3, R705.1
PTC_GATE: Q703.1, R705.2, R706.1
PTC_GPIO: R701.1, U202.8
PTC_NPN_B: Q701.1, R701.2, R702.1
PTC_NPN_C: Q701.3, R703.1
PTC_PNP_B: Q702.1, R703.2, R704.2
PUMP_DRAIN: D701.2, J702.2, Q704.3
PUMP_GATE: Q704.1, R707.2, R708.1
PUMP_GPIO: R707.1, U202.9
REVP_GATE: D103.1, Q102.1, R108.2
RTC_X1: C301.1, U301.1, Y301.1
RTC_X2: C302.1, U301.2, Y301.2
RTN_SHUNT: Q102.3, R111.2, R112.2, U102.9
SD_CS: J301.2, R303.2, U202.16
SD_DAT1: J301.8, R306.2
SD_DAT2: J301.1, R307.2
SD_MISO: J301.7, R305.2, U202.31
SD_MOSI: J301.3, R302.2, R304.2
SD_MOSI_GPIO: R302.1, U202.37
SD_SCK: J301.5, R301.2
SD_SCK_GPIO: R301.1, U202.30
SHT_SCL: J401.4, R402.2, U401.3, U401.4
SHT_SDA: J401.3, R401.2, U401.1, U401.6
UART_RX: J201.4, U202.34
UART_TX: J201.3, U202.35
VBAT: BT301.1, U301.3

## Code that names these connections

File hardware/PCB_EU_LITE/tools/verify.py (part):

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    check('No passive SMD footprint is smaller than 0603', all(not re.search(r'_(0201|0402)_', x['footprint']) for x in spec['parts'] if x['symbol'] in ['R', 'C', 'CP', 'L']))

    # ---- input, reverse polarity, power monitor
    check('Input terminal polarity, main fuse and TVS', pins('J101', {1: '+24V_RAW', 2: 'PSU_RTN'}) and pins('F101', {1: '+24V_RAW', 2: '+24V_FUSED'}) and pins('D101', {1: '+24V_FUSED', 2: 'GND'}) and p['D101']['mpn'] == 'SMBJ26A-E3/52')
    check('Reverse polarity: Q102 IRL2505 drain on PSU return, source on the shunt; PSU_RTN touches only J101.2 and Q102',
          pins('Q102', {1: 'REVP_GATE', 2: 'PSU_RTN', 3: 'RTN_SHUNT'}) and p['Q102']['mpn'] == 'IRL2505' and real('PSU_RTN') == {('J101', '2'), ('Q102', '2')})
    vgs = lambda vin: min(12.0, vin * 0.98 - 0.6)   # zener 12 V (5%), gate feed R108; loose bound for the low end
    check('Q102 gate clamp: 12 V zener keeps Vgs below the IRL2505 16 V limit up to the 42 V TVS clamp; >= 10 V enhancement at 21.6 V; R108 1206 power at 42 V <= 0.125 W',
          two('R108', '+24V_FUSED', 'REVP_GATE') and two('D103', 'REVP_GATE', 'GND') and p['D103']['mpn'] == 'BZV55C12' and 12 * 1.05 < 16 and vgs(21.6) >= 10
          and (42 - 12) ** 2 / val('R108') <= 0.125 and 'R_1206' in p['R108']['footprint'])
    rsh = par(ohm('7m'), ohm('7m'))
    check('Power monitor: INA238 U102 at I2C 0x40 (A0=A1=GND), 3.5 mOhm low-side shunt carries all return current',
          pins('U102', {1: 'GND', 2: 'GND', 4: 'I2C_SDA', 5: 'I2C_SCL', 6: '+3V3', 7: 'GND', 8: '+24V_FUSED', 9: 'RTN_SHUNT', 10: 'GND'}) and n('U102', 3) is None
          and all(two(x, 'GND', 'RTN_SHUNT') for x in ('R111', 'R112')) and abs(rsh - 0.0035) < 1e-9
          and real('RTN_SHUNT') == {('Q102', '3'), ('R111', '2'), ('R112', '2'), ('U102', '9')})
    i_max = 9.0
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
    # ---- 12 V buck
    check('ST1S14 pin map: VIN 7 on fused +24V_AUX, EN1 3 and GND 6/EP 9 on GND, EN2 5, FB 4, SW 8, BOOT 1, PG 2 open',
          pins('U101', {1: 'AUX_BOOT', 3: 'GND', 4: 'AUX_FB', 5: 'AUX_EN2', 6: 'GND', 7: '+24V_AUX', 8: 'AUX_SW', 9: 'GND'}) and n('U101', 2) is None and p['U101']['mpn'] == 'ST1S14PHR')
    check('ST1S14 power stage: bootstrap 100n BOOT-SW, 22 uH to +12V, SS56 catch diode (cathode SW), 820 uF + 10 uF + 100 nF output',
          two('C106', 'AUX_BOOT', 'AUX_SW') and two('L101', 'AUX_SW', '+12V') and pins('D102', {1: 'AUX_SW', 2: 'GND'}) and p['D102']['mpn'] == 'SS56'
          and two('C110', '+12V', 'GND') and two('C111', '+12V', 'GND') and two('C112', '+12V', 'GND') and p['C110']['mpn'] == 'EEEFT1E821AP')
    rt = val('R101') + val('R102'); rb = val('R103')
    v12 = [vfb * (1 + rt / rb) for vfb in (1.202, 1.222, 1.239)]
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
    # ---- 3.3 V buck and ESP32
    check('ST1S10 pin map: VIN_A 1, INH 2 and VIN_SW 6 on +12V, VFB 3, AGND 4, SYNC 5 on GND (900 kHz), SW 7, PGND 8, EP 9',
          pins('U201', {1: '+12V', 2: '+12V', 3: 'LOGIC_FB', 4: 'GND', 5: 'GND', 6: '+12V', 7: 'LOGIC_SW', 8: 'GND', 9: 'GND'}) and p['U201']['mpn'] == 'ST1S10PHR')
    rb33 = par(val('R202'), val('R203')); rt33 = val('R201')
    v33 = [vfb * (1 + rt33 / rb33) for vfb in (0.784, 0.8, 0.816)]
    check(f'+3V3 = 0.8 V x (1 + 100k / (47k||100k)) = {v33[1]:.2f} V ({v33[0]:.2f}-{v33[2]:.2f} V); ESP32 needs 3.0-3.6 V',
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    rip33 = 3.3 * (1 - 3.3 / 12) / (2.2e-6 * 900e3)
    check(f'ST1S10 with 2.2 uH: ripple {rip33:.2f} A (datasheet window 0.6-1.2 A at 3 A rating), peak at 1 A {1 + rip33 / 2:.2f} A < Isat 2.7 A, LC corner {flc / 1e3:.0f} kHz (datasheet design 18.7 kHz)',
          two('L201', 'LOGIC_SW', '+3V3') and p['L201']['mpn'] == 'SRN2512-2R2M' and rip33 <= 1.25 and 1 + rip33 / 2 < 2.7 and 15e3 < flc < 25e3)
    gpio = {6: 'FAN1_TACH', 7: 'FAN2_TACH', 8: 'PTC_GPIO', 9: 'PUMP_GPIO', 10: 'LED_PWM_GPIO', 11: 'FAN1_GPIO', 12: 'FAN2_GPIO', 13: 'FLOAT_GPIO', 16: 'SD_CS', 25: 'ESP_BOOT', 26: 'LED_R_GPIO', 27: 'LED_G_GPIO', 28: 'LED_B_GPIO', 30: 'SD_SCK_GPIO', 31: 'SD_MISO',
            33: 'I2C_SDA', 34: 'UART_RX', 35: 'UART_TX', 36: 'I2C_SCL', 37: 'SD_MOSI_GPIO'}
    check('ESP32 GPIO map is the EU-0.1 map; all four ground contacts, 3V3 and EN are consistent; GPIO34/35 have 10k pull-ups and no connector signal (tach removed)',
          pins('U202', dict(gpio, **{'1': 'GND', '15': 'GND', '38': 'GND', '39': 'GND', '2': '+3V3', '3': 'ESP_EN'})) and p['U202']['mpn'] == 'ESP32-WROOM-32E-N4')
    check('GPIO34/35 sit on 10k pull-ups only (nets reach no connector); the strapping pins 2/5/12/15 (module 24/29/14/23) carry no external load',
          two('R206', '+3V3', 'FAN1_TACH') and two('R207', '+3V3', 'FAN2_TACH') and val('R206') == val('R207') == 10e3 and real('FAN1_TACH') == {('U202', '6'), ('R206', '2')}
          and real('FAN2_TACH') == {('U202', '7'), ('R207', '2')} and all(n('U202', i) is None for i in (24, 29, 14, 23)))
    check('UART service connector has the EU-0.1 3.3 V pin order', pins('J201', {1: 'GND', 2: '+3V3', 3: 'UART_TX', 4: 'UART_RX', 5: 'ESP_EN', 6: 'ESP_BOOT'}))
    check('BOOT / EN have external pull-ups and active-low buttons; EN delay 10k / 2.2u (Espressif: 10k / 1u or more)',
          pins('C209', {1: 'ESP_EN', 2: 'GND'}) and two('R204', '+3V3', 'ESP_EN') and two('R205', '+3V3', 'ESP_BOOT') and pins('SW201', {1: 'ESP_EN', 2: 'GND'}) and pins('SW202', {1: 'ESP_BOOT', 2: 'GND'}) and val('R204') == 10e3)

    # ---- RTC, SD, interfaces
    check('RTC battery is isolated from 3.3 V; MCP7940N pin 3 VBAT / pin 8 VCC; MFP unused',
          pins('U301', {1: 'RTC_X1', 2: 'RTC_X2', 3: 'VBAT', 4: 'GND', 5: 'I2C_SDA', 6: 'I2C_SCL', 8: '+3V3'}) and n('U301', 7) is None and real('VBAT') == {('U301', '3'), ('BT301', '1')})
    sd_lines = ['SD_CS', 'SD_MOSI', 'SD_MISO', 'SD_DAT1', 'SD_DAT2']
    check('All five SD CMD/DAT lines have external 10k pull-ups to +3V3', all(any(x['symbol'] == 'R' and two(x['ref'], '+3V3', net) and val(x['ref']) == 10e3 for x in p.values()) for net in sd_lines))
    check('SD SPI pin mapping and shell ground follow the GCT MEM2061 drawing; SCK/MOSI have 100 R series resistors',
          pins('J301', {1: 'SD_DAT2', 2: 'SD_CS', 3: 'SD_MOSI', 4: '+3V3', 5: 'SD_SCK', 6: 'GND', 7: 'SD_MISO', 8: 'SD_DAT1', 'SH': 'GND'}) and two('R301', 'SD_SCK_GPIO', 'SD_SCK') and two('R302', 'SD_MOSI_GPIO', 'SD_MOSI') and val('R301') == 100)
    check('I2C has 4.7k pull-ups; SHT4x header: 1 +3V3, 2 GND, 3 SDA, 4 SCL behind 100 R and USBLC6 U401 (ref pin 5 on +3V3)',
          two('R308', '+3V3', 'I2C_SDA') and two('R309', '+3V3', 'I2C_SCL') and pins('J401', {1: '+3V3', 2: 'GND', 3: 'SHT_SDA', 4: 'SHT_SCL'}) and two('R401', 'I2C_SDA', 'SHT_SDA') and two('R402', 'I2C_SCL', 'SHT_SCL')
          and pins('U401', {1: 'SHT_SDA', 6: 'SHT_SDA', 3: 'SHT_SCL', 4: 'SHT_SCL', 2: 'GND', 5: '+3V3'}) and val('R308') == 4700)
    check('Float input: series 1k, 10k pull-up and 100n filter to GPIO14; no USBLC6 on this line (documented trade-off)',
          two('R403', 'FLOAT_EXT', 'FLOAT_GPIO') and two('R404', '+3V3', 'FLOAT_GPIO') and pins('C403', {1: 'FLOAT_GPIO', 2: 'GND'}) and pins('J403', {1: 'FLOAT_EXT', 2: 'GND'}) and 'U402' not in p)
    for k, b in [(1, 410), (2, 420)]:
        pre = f'FAN{k}'
        check(f'Fan{k}: AO3422 source pin 2 grounded, 100k reset pull-down, 1k gate; header 1 GND, 2 +12 V, 3 tach NC, 4 PWM; no tach signal, no ESD part',
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
    # ---- LED boost (one channel)
    check('LM3429 pin map: VIN on its fused 24 V, nDIM shared net, EP/PGND/AGND on GND, GATE_RAW, VCC, IS, HSP, HSN',
          pins('U501', {1: '+24V_LED', 2: 'LED_COMP', 3: 'LED_CSH', 4: 'LED_RCT', 5: 'GND', 6: 'LED_OVP', 7: 'LED_NDIM', 9: 'GND', 10: 'LED_GATE_RAW', 11: 'LED_VCC', 12: 'LED_IS', 13: 'LED_HSP', 14: 'LED_HSN', 15: 'GND'}) and n('U501', 8) is None)
    check('Boost power stage: 47 uH from fused 24 V to SW, SBRT15U100SP5 cathode on OUT, BSC146N10LS5 drain SW / gate / source on the IS shunt to GND',
          pins('L501', {1: '+24V_LED', 2: 'LED_SW'}) and pins('D501', {1: 'LED_OUT', 2: 'LED_SW'}) and p['D501']['mpn'].startswith('SBRT15U100SP5')
          and pins('Q501', {1: 'LED_IS', 2: 'LED_IS', 3: 'LED_IS', 4: 'LED_GATE', 5: 'LED_SW'}) and p['Q501']['mpn'] == 'BSC146N10LS5' and two('R501', 'LED_IS', 'GND'))
    check('LED return is GND; output bank (470u/63V + six 4u7/100V + 100n/100V) is before the high-side LED shunt; HSP/HSN use equal 1k filters',
          pins('J501', {1: 'LED_POS', 2: 'GND'}) and two('R502', 'LED_OUT', 'LED_POS') and two('R503', 'LED_OUT', 'LED_HSP') and two('R504', 'LED_POS', 'LED_HSN') and val('R503') == val('R504') == 1000
          and all(n(r_, 1) == 'LED_OUT' and n(r_, 2) == 'GND' for r_, x in p.items() if x['sheet'] == 'LED' and x['mpn'] in ('EEVFK1J471M', 'CL32B475KCI6PJE', 'KAF21KR72A104KL'))
          and sum(1 for x in p.values() if x['mpn'] == 'CL32B475KCI6PJE') == 6)
    led_terminals = ('J501', 'J502', 'J503')
    check('J501/J502/J503 are parallel stock KF301 terminals after R502, sharing one current-controlled LED output without bypassing its shunt',
          all(pins(ref, {1: 'LED_POS', 2: 'GND'}) and p[ref]['src'] == 'S93' and p[ref]['in_bom']
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

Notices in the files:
hardware/PCB_EU_LITE/tools/verify.py:
SPDX-License-Identifier: MIT
